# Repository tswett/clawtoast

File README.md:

This is the repository for Clawtoast, a project to create a modular testing
system for electronics.

By publishing a modified version of this repository, you automatically license
your modified version according to the copyright information below. If you do
not wish to license your modified version under those terms, you must modify
this README file to remove all license statements that you disagree with. Note
that publishing a modified version without releasing your modified version under
the GNU GPL v3 may be a violation of copyright law.

## Warnings and disclaimers

Warning: The software, instructions, and other contents of this repository are
likely to contain serious errors. Following the instructions in this repository,
or using the software or other contents of this repository, may damage or
destroy any or all connected devices. Do so at your own risk!

This repository is distributed in the hope that it will be useful, but WITHOUT
ANY WARRANTY; without even the implied warranty of MERCHANTABILITY or FITNESS
FOR A PARTICULAR PURPOSE. See the GNU General Public License for more details.

The above warning and disclaimer of warranty apply to the entire contents of
this repository, regardless of whether or not any additional warranty or
disclaimer is present in any individual file.

# Copyright information

This file (README.md) is copyright 2023 Tanner Swett.

This file is part of Clawtoast. Clawtoast is free software: you can redistribute
it and/or modify it under the terms of version 3 of the GNU General Public
License as published by the Free Software Foundation.

To the extent to which it is legally possible, all of the contributors to this
repository release the entire contents of this repository, and every part of the
contents of this repository, under the GNU GPL v3. Note that this repository may
contain files that were authored by other people and copied into it
automatically as part of a template, and such files may or may not be licensed
under the GNU GPL v3. The lack of a license statement in a particular file may
indicate that it is such a file.

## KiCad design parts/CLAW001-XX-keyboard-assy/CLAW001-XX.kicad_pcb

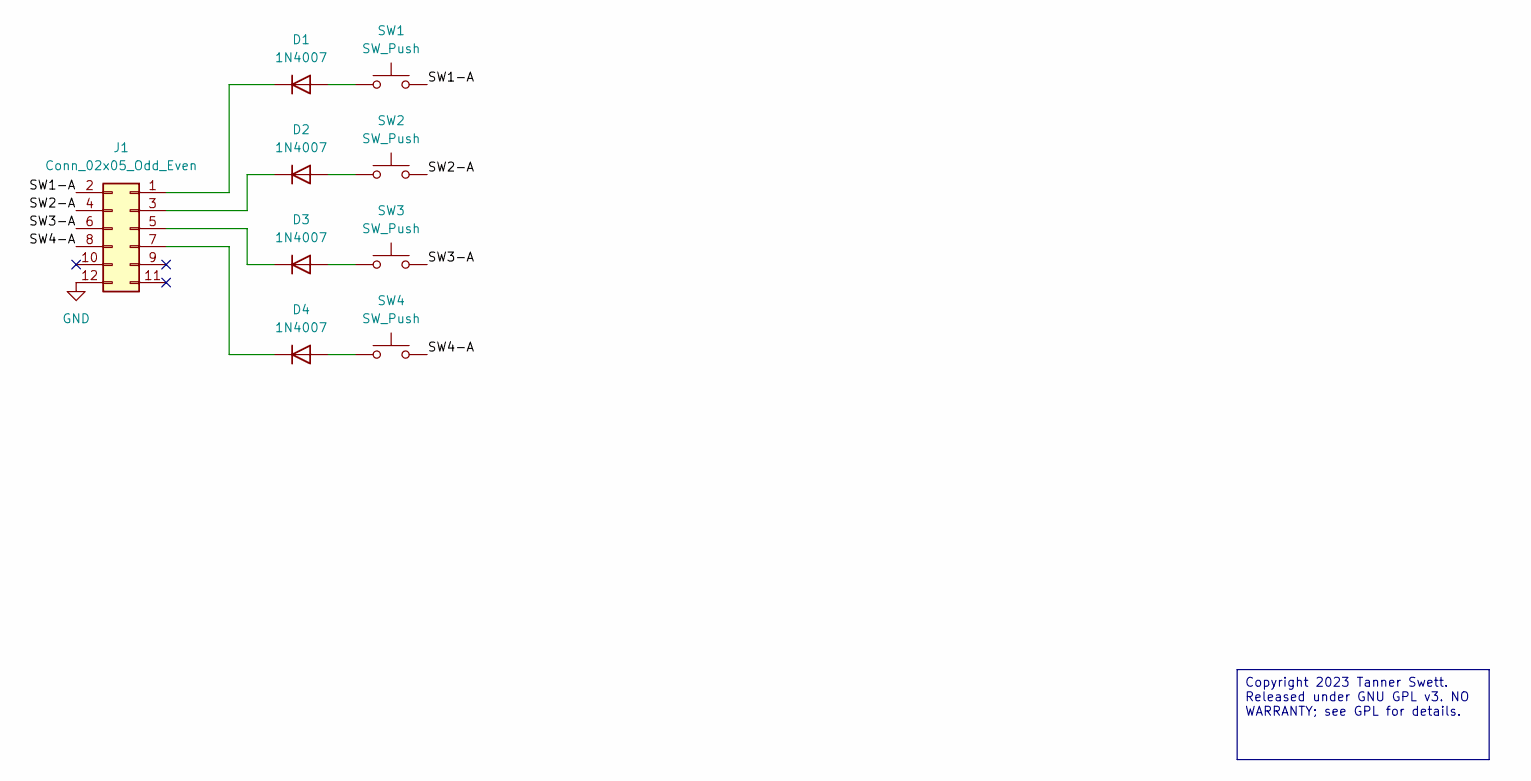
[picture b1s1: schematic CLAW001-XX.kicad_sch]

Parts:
D1, D2, D3, D4: 1N4007; D_DO-41_SOD81_P10.16mm_Horizontal
J1: Conn_02x05_Odd_Even; PinHeader_2x06_P2.54mm_Vertical
SW1, SW2, SW3, SW4: SW_Push; 1528-4954-ND

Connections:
/SW1-A: J1.2, SW1.2
/SW2-A: J1.4, SW2.2
/SW3-A: J1.6, SW3.2
/SW4-A: J1.8, SW4.2
GND: J1.12
unnamed: D1.2 (A), SW1.1
unnamed: D1.1 (K), J1.1
unnamed: D2.2 (A), SW2.1
unnamed: D2.1 (K), J1.3
unnamed: D3.2 (A), SW3.1
unnamed: D3.1 (K), J1.5
unnamed: D4.2 (A), SW4.1
unnamed: D4.1 (K), J1.7

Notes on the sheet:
Copyright 2023 Tanner Swett. Released under GNU GPL v3. NO WARRANTY; see GPL for details.

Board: 2 copper layers, 9 parts (0 on the bottom side), 12 nets, no tracks yet.

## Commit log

2023-11-17 Initial commit, with blinking lights
2023-11-17 Add E002: "remote programming" experiment
    Add instructions on how to use the ST-Link on one Nucleo board to
    program the other Nucleo board.
2023-11-17 E002: Add missing NRST wire to diagram
2023-11-18 Add E003: a test-driven development experiment
    Here's a little Python script which uses pyOCD to connect to the Nucleo
    board and then runs automated tests on it.
2023-11-19 Initial commit for P001 (NAND gate project)
2023-11-19 Add pyproject.toml files and such
2023-11-19 P001: Implement the very beginnings of steamer
    Write just enough code to make it easy to check what the mode of a GPIO
    pin is set to.
2023-12-12 Start designing CLAW001-XX keyboard assembly
2023-12-13 P001: Update Poetry lockfile
2023-12-13 Add Pyright to the Python library and start fixing type errors
2023-12-13 Fix most of the Pyright errors
